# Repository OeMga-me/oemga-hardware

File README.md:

<h1 align="center">OeMga.me Hardware</h1>

<p align="center">

</p>

<p align="center">
<strong>The open-source, on-device teachable bio-interaction platform.</strong>
</p>

Copyright 2026 Adithya Pamulaparthi. Licensed under CERN-OHL-S v2.

[View Interactive 3D Model](hardware/CAD/Assembly.STL)

## The Vision
Current wearables demand that we speak their language. OeMga.me learns ours.

Today’s bio-sensors with rigid FSMs and pre-trained models, force the user to conform to the machine’s limitations. OeMga.me dismantles this paradigm. We are building the first **Teachable Bio-Interaction Platform**, where intelligence lives at the edge and evolves with you.

## The Foundation: OeMga $\alpha$
This repository hosts the open-source hardware files for the foundational module of the OeMga $\alpha$ platform: a high-precision, teachable EMG sensor.

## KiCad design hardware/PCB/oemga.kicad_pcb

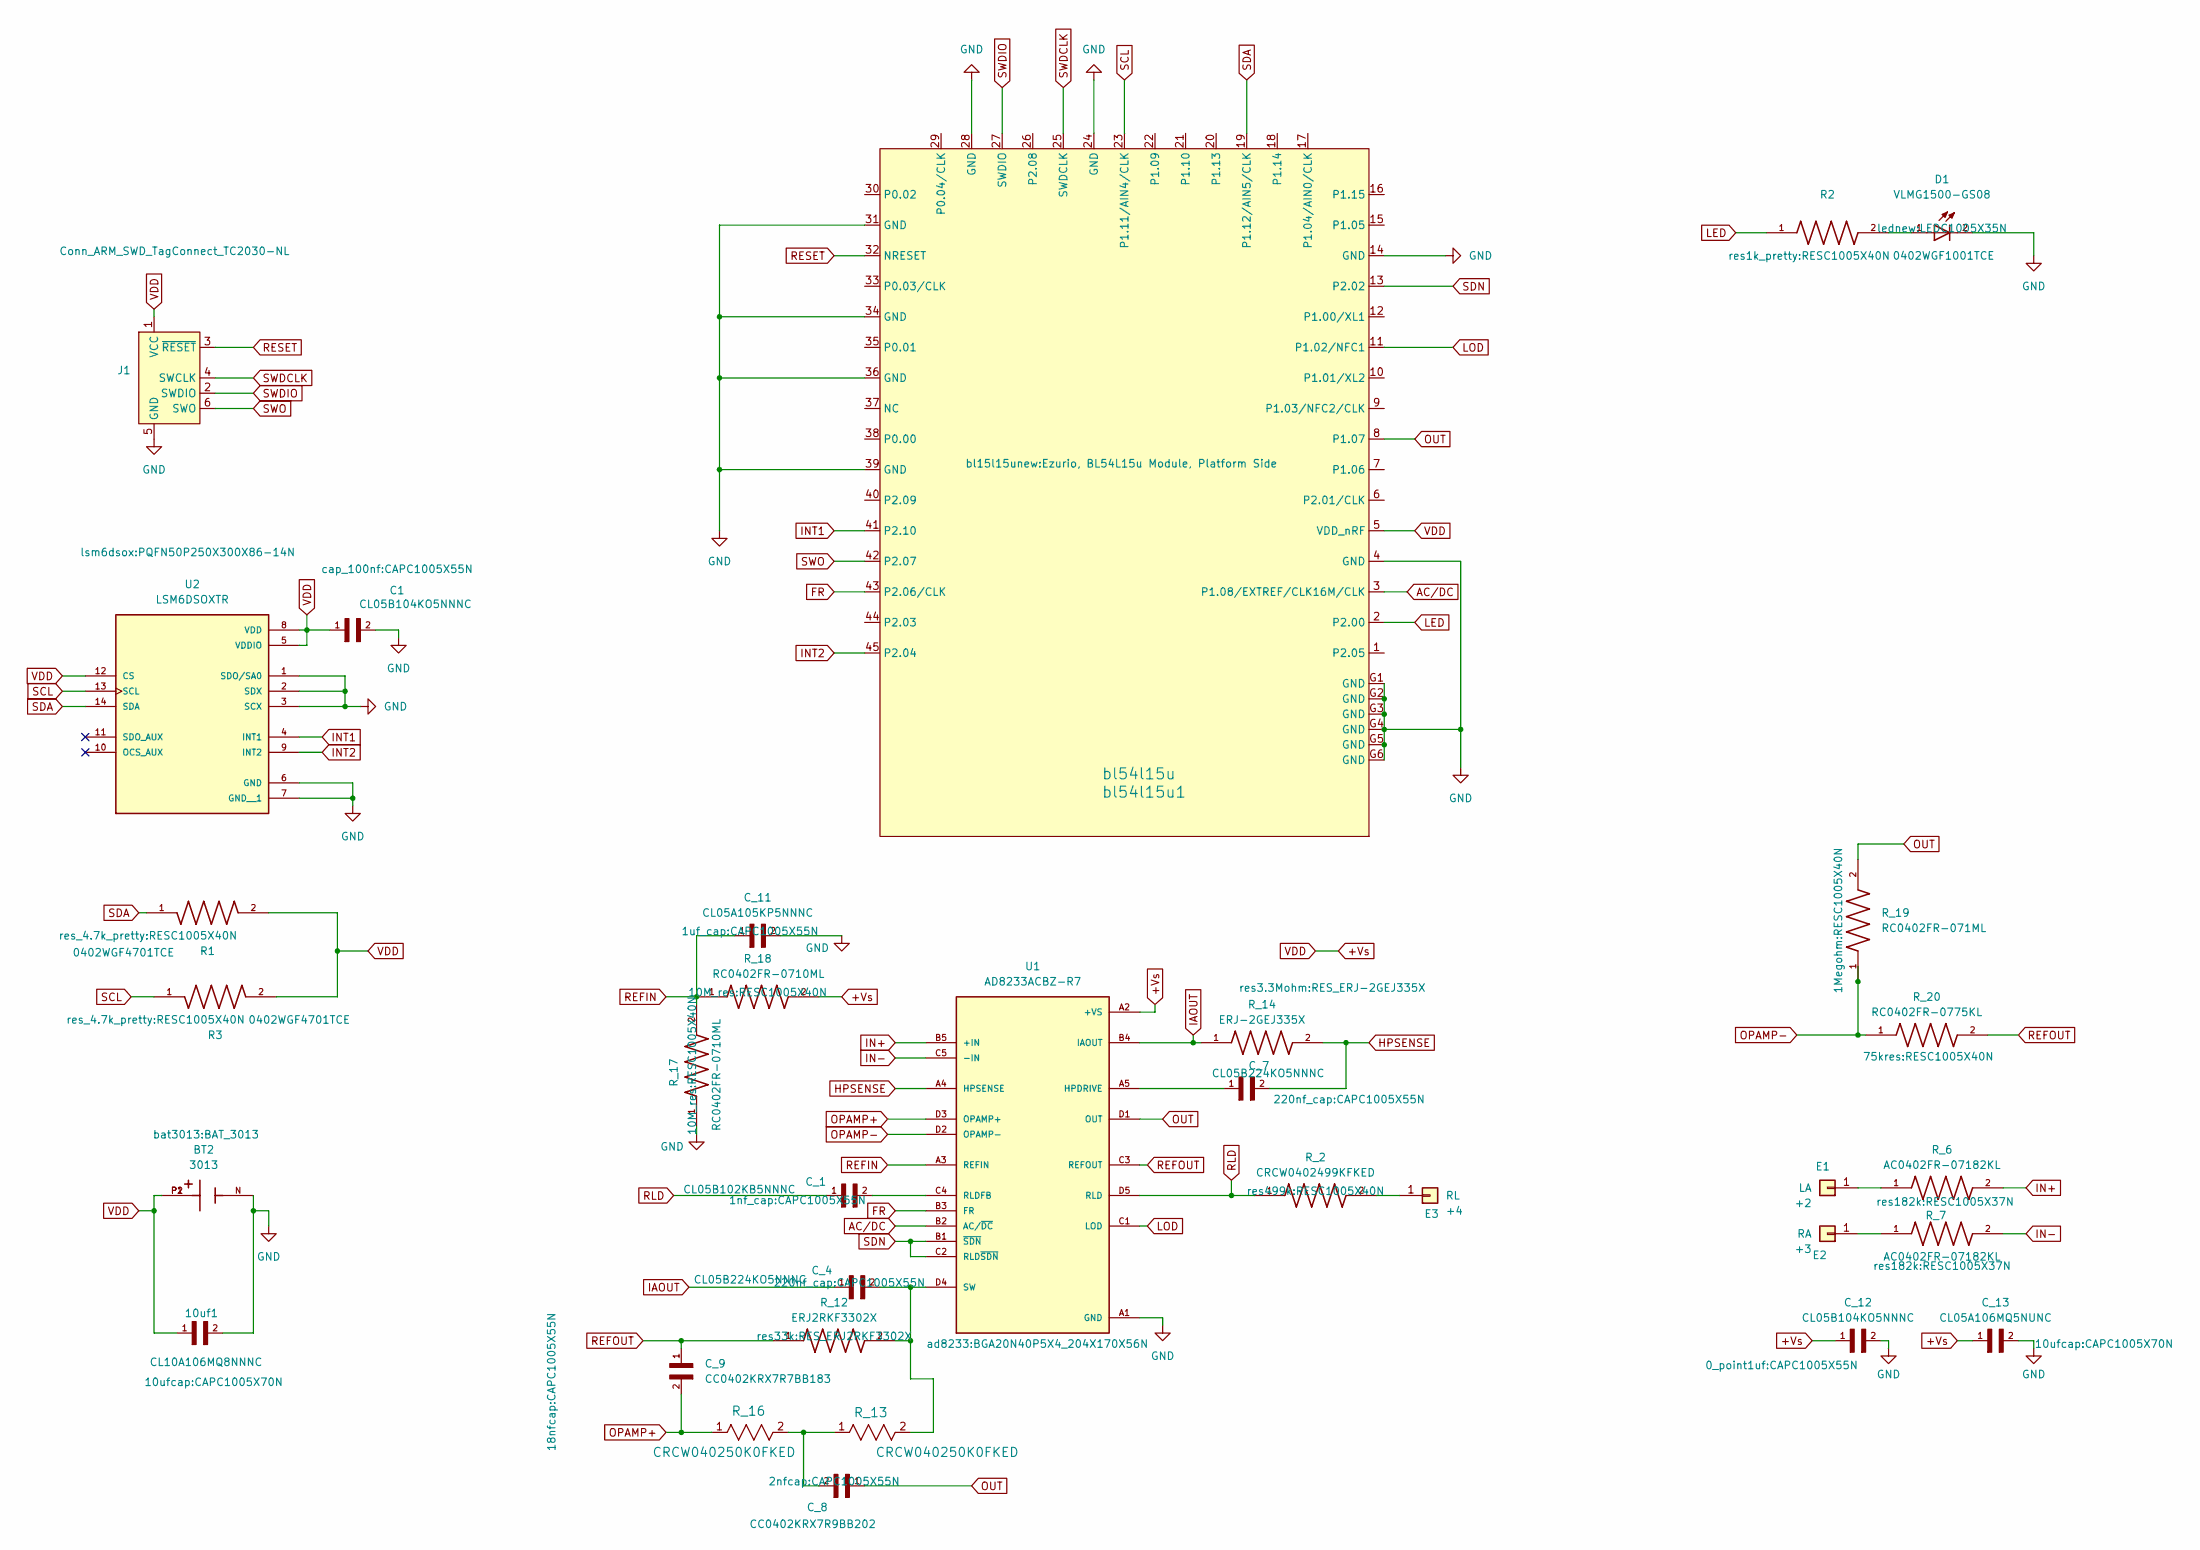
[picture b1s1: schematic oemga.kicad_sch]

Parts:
10uf1: CL10A106MQ8NNNC; CAPC1005X70N
+2: LA; E1
+3: RA; E2
+4: RL; E3
BT2: 3013; BAT_3013; PARTREV E
C1: CL05B104KO5NNNC; CAPC1005X55N
C_1: CL05B102KB5NNNC; CAPC1005X55N
C_4, C_7: CL05B224KO5NNNC; CAPC1005X55N
C_8: CC0402KRX7R9BB202; CAPC1005X55N; DigiKey_Part_Number 13-CC0402KRX7R9BB202CT-ND
C_9: CC0402KRX7R7BB183; CAPC1005X55N; DigiKey_Part_Number 311-1706-1-ND
C_11: CL05A105KP5NNNC; CAPC1005X55N
C_12: CL05B104KO5NNNC; CAPC1005X55N
C_13: CL05A106MQ5NUNC; CAPC1005X70N
D1: VLMG1500-GS08; LEDC1005X35N; PARTREV 1.4
J1: Conn_ARM_SWD_TagConnect_TC2030-NL; Tag-Connect_TC2030-IDC-NL_2x03_P1.27mm_Vertical
R1, R3: 0402WGF4701TCE; RESC1005X40N; PARTREV V3
R2: 0402WGF1001TCE; RESC1005X40N; PARTREV V3
R_2: CRCW0402499KFKED; RESC1005X40N
R_6, R_7: AC0402FR-07182KL; RESC1005X37N; DigiKey_Part_Number 13-AC0402FR-07182KLCT-ND
R_12: ERJ2RKF3302X; RES_ERJ2RKF3302X; PARTREV 3/1/2020
R_13, R_16: CRCW040250K0FKED; RES_CRCW0402_VIS
R_14: ERJ-2GEJ335X; RES_ERJ-2GEJ335X; PARTREV 3/1/2020
R_17, R_18: RC0402FR-0710ML; RESC1005X40N
R_19: RC0402FR-071ML; RESC1005X40N; PARTREV Nov-2024; DigiKey_Part_Number 311-1.00MLRCT-ND
R_20: RC0402FR-0775KL; RESC1005X40N; DigiKey_Part_Number 311-75KLRCT-ND
U1: AD8233ACBZ-R7; BGA20N40P5X4_204X170X56N; PARTREV 0
U2: LSM6DSOXTR; PQFN50P250X300X86-14N; PARTREV 3.0
bl54l15u1: bl54l15u; Ezurio, BL54L15u Module, Platform Side

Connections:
+Vs: 10uf1.1, BT2.P1, BT2.P2, C1.1, C_12.1, C_13.1, J1.1 (VCC), R1.2, R3.2, R_18.2, U1.A2 (+VS), U2.5 (VDDIO), U2.8 (VDD), U2.12 (CS), bl54l15u1.5 (VDD_nRF)
AC/DC: U1.B2 (AC/~DC), bl54l15u1.3 (P1.08/EXTREF/CLK16M/CLK)
FR: U1.B3 (FR), bl54l15u1.43 (P2.06/CLK)
GND: 10uf1.2, BT2.N, C1.2, C_11.2, C_12.2, C_13.2, D1.2, J1.5 (GND), R_17.1, U1.A1 (GND), U2.1 (SDO/SA0), U2.2 (SDX), U2.3 (SCX), U2.6 (GND), U2.7 (GND__1), bl54l15u1.4 (GND), bl54l15u1.14 (GND), bl54l15u1.24 (GND), bl54l15u1.28 (GND), bl54l15u1.31 (GND), bl54l15u1.34 (GND), bl54l15u1.36 (GND), bl54l15u1.39 (GND), bl54l15u1.G1 (GND), bl54l15u1.G2 (GND), bl54l15u1.G3 (GND), bl54l15u1.G4 (GND), bl54l15u1.G5 (GND), bl54l15u1.G6 (GND)
HPSENSE: C_7.2, R_14.2, U1.A4 (HPSENSE)
IAOUT: C_4.1, R_14.1, U1.B4 (IAOUT)
IN+: R_6.2, U1.B5 (+IN)
IN-: R_7.2, U1.C5 (-IN)
INT1: U2.4 (INT1), bl54l15u1.41 (P2.10)
INT2: U2.9 (INT2), bl54l15u1.45 (P2.04)
LED: R2.1, bl54l15u1.2 (P2.00)
LOD: U1.C1 (LOD), bl54l15u1.11 (P1.02/NFC1)
unnamed: +2.1, R_6.1
unnamed: +3.1, R_7.1
unnamed: +4.1, R_2.2
unnamed: C_8.2, R_13.1, R_16.2
unnamed: D1.1, R2.2
unnamed: C_7.1, U1.A5 (HPDRIVE)
unnamed: C_1.2, U1.C4 (RLDFB)
unnamed: C_4.2, R_12.2, R_13.2, U1.D4 (SW)
OPAMP+: C_9.2, R_16.1, U1.D3 (OPAMP+)
OPAMP-: R_19.1, R_20.1, U1.D2 (OPAMP-)
OUT: C_8.1, R_19.2, U1.D1 (OUT), bl54l15u1.8 (P1.07)
REFIN: C_11.1, R_17.2, R_18.1, U1.A3 (REFIN)
REFOUT: C_9.1, R_12.1, R_20.2, U1.C3 (REFOUT)
RESET: J1.3 (~RESET), bl54l15u1.32 (NRESET)
RLD: C_1.1, R_2.1, U1.D5 (RLD)
SCL: R3.1, U2.13 (SCL), bl54l15u1.23 (P1.11/AIN4/CLK)
SDA: R1.1, U2.14 (SDA), bl54l15u1.19 (P1.12/AIN5/CLK)
SDN: U1.B1 (~SDN), U1.C2 (RLD~SDN), bl54l15u1.13 (P2.02)
SWDCLK: J1.4 (SWCLK), bl54l15u1.25 (SWDCLK)
SWDIO: J1.2 (SWDIO), bl54l15u1.27 (SWDIO)
SWO: J1.6 (SWO), bl54l15u1.42 (P2.07)

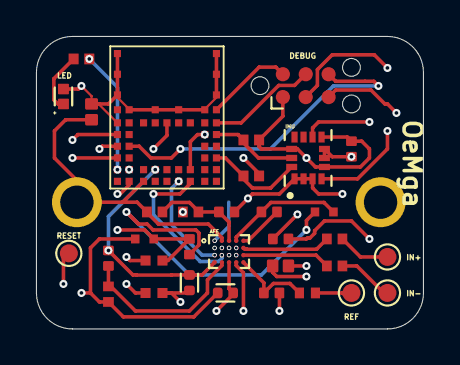
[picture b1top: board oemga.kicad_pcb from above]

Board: 6 copper layers, 21.5 x 16.2 mm, 30 parts (1 on the bottom side), 30 nets.

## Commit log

2026-02-03 Create LICENSE
2026-02-03 Rename LICENSE to LICENSE.txt
2026-02-03 Initial release: v1.0 hardware with CERN-OHL-S license
2026-02-03 Remove .DS_Store junk file
2026-02-03 Initial release: v1.0 CAD
2026-02-03 Assembly STL

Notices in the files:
README.md:
License: CERN-OHL-S v2
